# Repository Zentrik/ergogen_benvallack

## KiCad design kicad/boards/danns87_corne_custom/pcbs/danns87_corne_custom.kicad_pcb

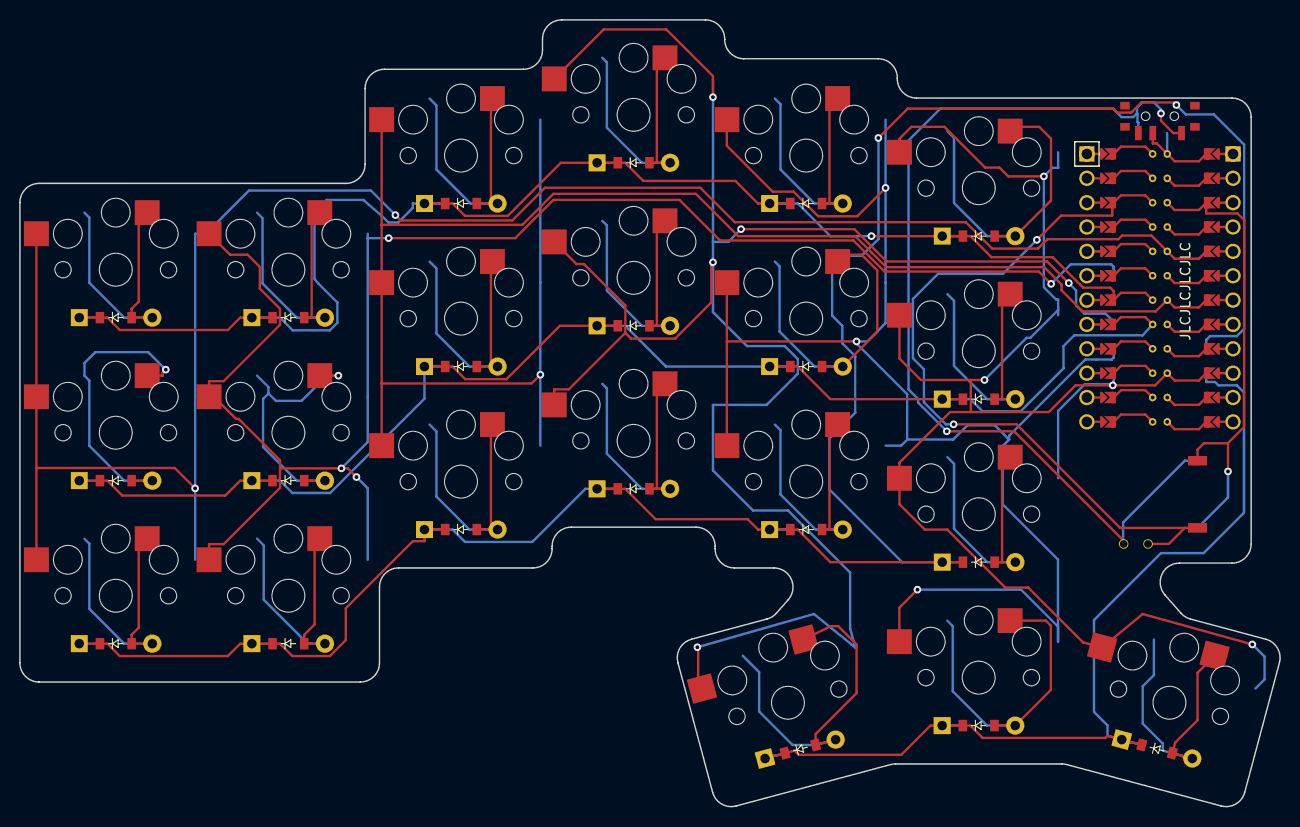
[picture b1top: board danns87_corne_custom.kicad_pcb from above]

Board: 2 copper layers, 131.4 x 82.0 mm, 46 parts (0 on the bottom side), 35 nets.

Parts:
D1, D2, D3, D4, D5, D6, D7, D8, D9, D10, D11, D12, D13, D14, D15, D16, D17, D18, D19, D20, D21: ComboDiode
MCU1: ProMicro
PAD1: bat2p54
S1, S2, S3, S4, S5, S6, S7, S8, S9, S10, S11, S12, S13, S14, S15, S16, S17, S18, S19, S20, S21: PG1350
S22: SW_SPST_UXCELL
T1: SW_SPDT_PCM12

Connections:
GND: MCU1.2, MCU1.21, MCU1.22, PAD1.2, S22.2
P4: D3.1, D3.2, D6.1, D6.2, D9.1, D9.2, D12.1, D12.2, D15.1, D15.2, D18.1, D18.2, MCU1.18
P5: D2.1, D2.2, D5.1, D5.2, D8.1, D8.2, D11.1, D11.2, D14.1, D14.2, D17.1, D17.2, MCU1.17
P6: D1.1, D1.2, D4.1, D4.2, D7.1, D7.2, D10.1, D10.2, D13.1, D13.2, D16.1, D16.2, MCU1.16
P7: D19.1, D19.2, D20.1, D20.2, D21.1, D21.2, MCU1.15
P14: MCU1.10, S16.2, S17.2, S18.2, S21.2
P15: MCU1.9, S13.2, S14.2, S15.2, S20.2
P18: MCU1.8, S10.2, S11.2, S12.2, S19.2
P19: MCU1.7, S7.2, S8.2, S9.2
P20: MCU1.6, S4.2, S5.2, S6.2
P21: MCU1.5, S1.2, S2.2, S3.2
RAW: MCU1.1, T1.2
RST: MCU1.3, S22.1
far_thumb: D21.1, D21.2, S21.1
home_thumb: D20.1, D20.2, S20.1
index_bottom: D13.1, D13.2, S13.1
index_home: D14.1, D14.2, S14.1
index_top: D15.1, D15.2, S15.1
inner_bottom: D16.1, D16.2, S16.1
inner_home: D17.1, D17.2, S17.1
inner_top: D18.1, D18.2, S18.1
middle_bottom: D10.1, D10.2, S10.1
middle_home: D11.1, D11.2, S11.1
middle_top: D12.1, D12.2, S12.1
near_thumb: D19.1, D19.2, S19.1
outer_bottom: D1.1, D1.2, S1.1
outer_home: D2.1, D2.2, S2.1
outer_top: D3.1, D3.2, S3.1
pinky_bottom: D4.1, D4.2, S4.1
pinky_home: D5.1, D5.2, S5.1
pinky_top: D6.1, D6.2, S6.1
pos: PAD1.1, T1.1
ring_bottom: D7.1, D7.2, S7.1
ring_home: D8.1, D8.2, S8.1
ring_top: D9.1, D9.2, S9.1

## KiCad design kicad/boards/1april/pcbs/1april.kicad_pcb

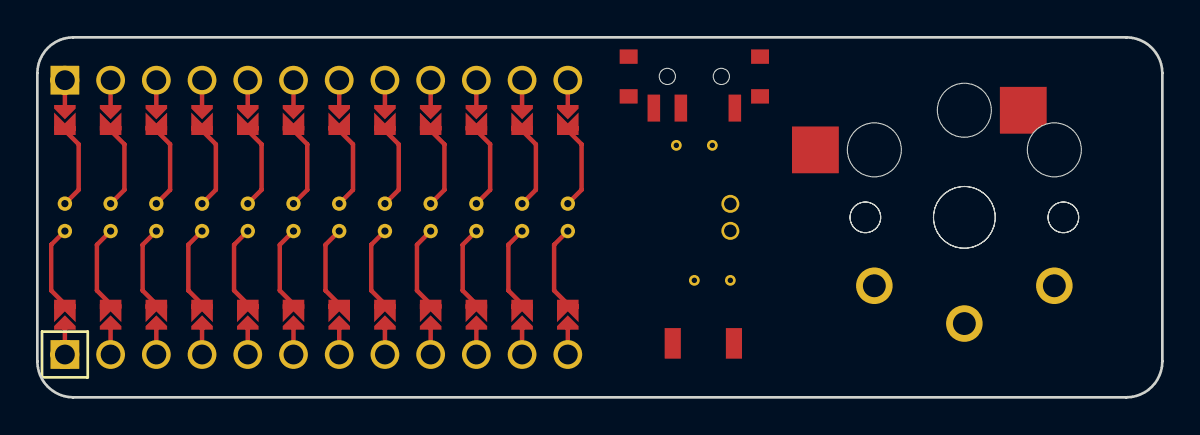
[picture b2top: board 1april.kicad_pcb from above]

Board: 2 copper layers, 62.5 x 20.0 mm, 3 parts (0 on the bottom side), 2 nets, no tracks yet.

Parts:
MCU1: ProMicro
S1, S2: PG1350

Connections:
GND: MCU1.2, MCU1.21, MCU1.22, S1.2, S2.2
P1: MCU1.24, S1.1, S2.1

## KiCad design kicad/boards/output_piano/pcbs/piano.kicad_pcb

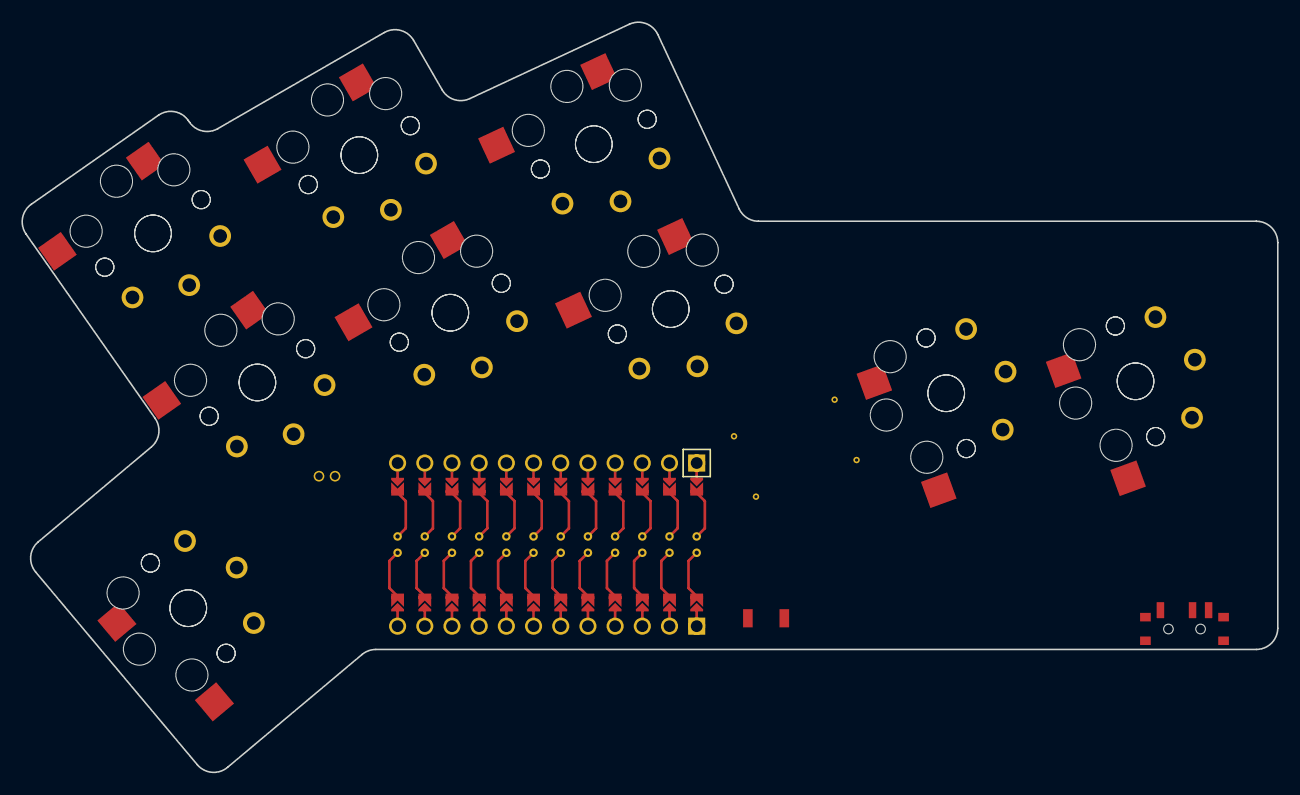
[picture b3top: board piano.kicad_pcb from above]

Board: 2 copper layers, 117.3 x 70.1 mm, 19 parts (0 on the bottom side), 10 nets, no tracks yet.

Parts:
MCU1: ProMicro
S1, S2, S3, S4, S5, S6, S7, S8, S9, S10, S11, S12, S13, S14, S15, S16, S17, S18: PG1350

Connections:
GND: MCU1.2, MCU1.21, MCU1.22, S1.2, S2.2, S3.2, S4.2, S5.2, S6.2, S7.2, S8.2, S9.2, S10.2, S11.2, S12.2, S13.2, S14.2, S15.2, S16.2, S17.2, S18.2
P0: MCU1.23, S15.1, S16.1
P1: MCU1.24, S17.1, S18.1
P4: MCU1.18, S11.1, S12.1
P5: MCU1.17, S13.1, S14.1
P8: MCU1.14, S5.1, S6.1
P9: MCU1.13, S3.1, S4.1
P10: MCU1.12, S1.1, S2.1
P14: MCU1.10, S9.1, S10.1
P15: MCU1.9, S7.1, S8.1

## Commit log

2022-06-26 Add rotation capability to pcm12 footprint
2022-06-26 Add uxcell smd reset button footprint -- guesstimated dimensions for now
2022-06-26 Add samoklava yaml, plus a modified version that actually compiles
2022-06-26 Add a placeholder kicad project with a few compiled boards
2022-06-26 Add base file for eventual Corne clone -- does not work yet
2022-06-26 Add footprint for 2.54mm spaced JST header
2022-06-26 danns87_corne: Add battery JST connector
2022-06-27 danns87_corne: Update key switch layouts to approximate Corne
2022-06-27 danns87_corne: Start working on outlines -- not done yet
2022-06-30 danns87_corne: Almost functional
2022-07-02 danns87_corne: Perfectly matching Chocorne key switches positions
2022-07-02 danns87_corne_custom: Add yaml, unfinished
2022-07-02 danns87_corne_custom: Clean up outline section
2022-07-03 danns87_corne_custom: Done keys and components layout
2022-07-03 Add missing footprint references
2022-07-03 danns87_corne_custom: Fix netlist issues
2022-07-03 danns87_corne_custom: Pad PCB cutout to make more room of some pads
2022-07-03 danns87_corne_custom: PCB tracks added, DRC passes with warnings, and, I think, ready for mfg
2022-07-03 danns87_corne_custom: Added JLC silk screen order number placeholder
2022-07-16 Increase drill hole for footprint 2.54mm spaced JST header from 0.7mm to 0.8mm
2022-07-16 danns87_corne_custom: Increase JST drill hole to 0.8mm and shift in X axis to avoid collision with microcontroller legs
2022-07-16 danns87_corne_custom: Update gerber files
2022-08-02 Remove empty lines
2022-08-02 First commit of custom boards.
    Test github actions.
2022-08-02 Add github actions from samoklava repo.
2022-08-02 Fixed github actions?
2022-08-02 Fix previous commit
    Who knew you could fuck up one line that badly.
2022-08-02 Fix output folder and hopefully fix X11 bug.
2022-08-02 Hopefully fix actions?
2022-08-02 Actions were not fixed, disable actions until samoklava repo is fixed.
2022-08-04 Thumb cluster not done.
2022-08-06 Thumb cluster good, only pinky and ring need fixing.
2022-08-18 Ignore kicad folder
2022-08-18 Finished pro micro board
2022-08-18 Added xiao footprint
2022-08-25 Set pins for xiao, finished.
2022-10-03 move battery connector down, add humming bird picture.
    Tried adding board with two split sides, better to just use kikit to panelize then flip, and manually add tabs.
2022-10-03 Remove both file, see previous commit message.
